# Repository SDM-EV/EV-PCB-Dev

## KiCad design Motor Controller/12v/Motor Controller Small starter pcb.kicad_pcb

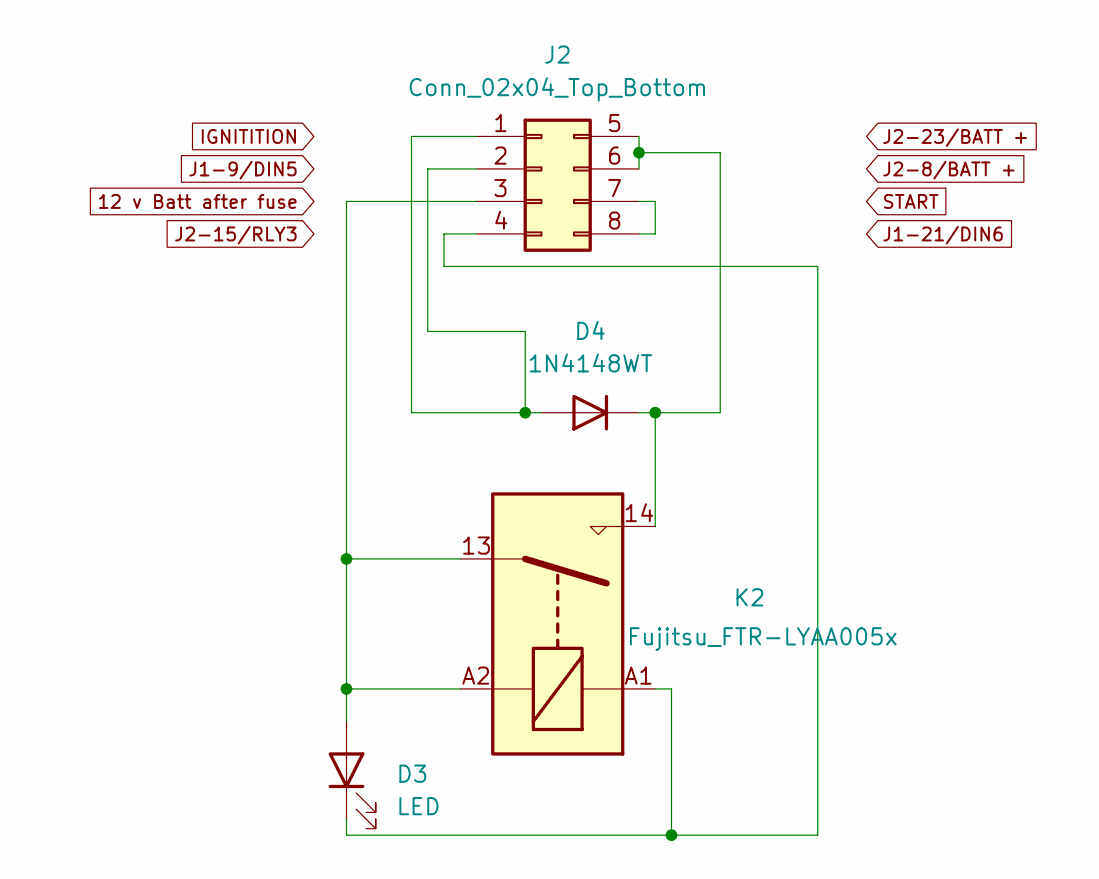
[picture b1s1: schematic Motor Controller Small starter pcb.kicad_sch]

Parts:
D3: LED; LED_D3.0mm
D4: 1N4148WT; D_SOD-523
J2: Conn_02x04_Top_Bottom; Molex_Mini-Fit_Jr_5566-08A2_2x04_P4.20mm_Vertical
K2: Fujitsu_FTR-LYAA005x; Relay_SPST-NO_Fujitsu_FTR-LYAA005x_FormA_Vertical

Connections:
unnamed: D3.2 (A), J2.3, K2.13, K2.A2
unnamed: D3.1 (K), J2.4, K2.A1
unnamed: D4.2 (A), J2.1, J2.2
unnamed: D4.1 (K), J2.5, J2.6, K2.14
unnamed: J2.7, J2.8

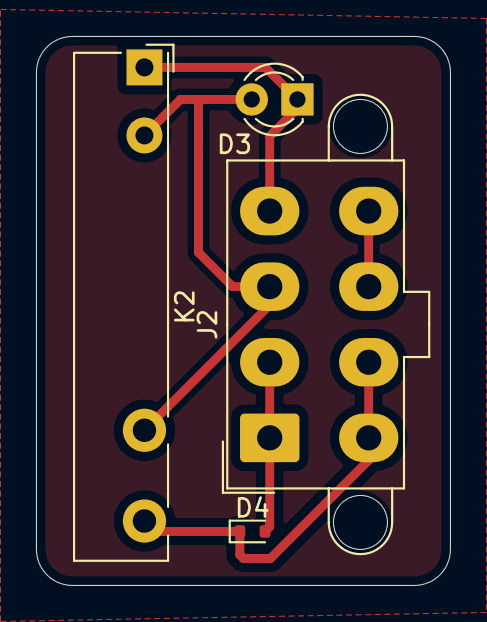
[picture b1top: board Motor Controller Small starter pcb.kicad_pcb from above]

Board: 2 copper layers, 23.0 x 30.5 mm, 4 parts (0 on the bottom side), 5 nets.

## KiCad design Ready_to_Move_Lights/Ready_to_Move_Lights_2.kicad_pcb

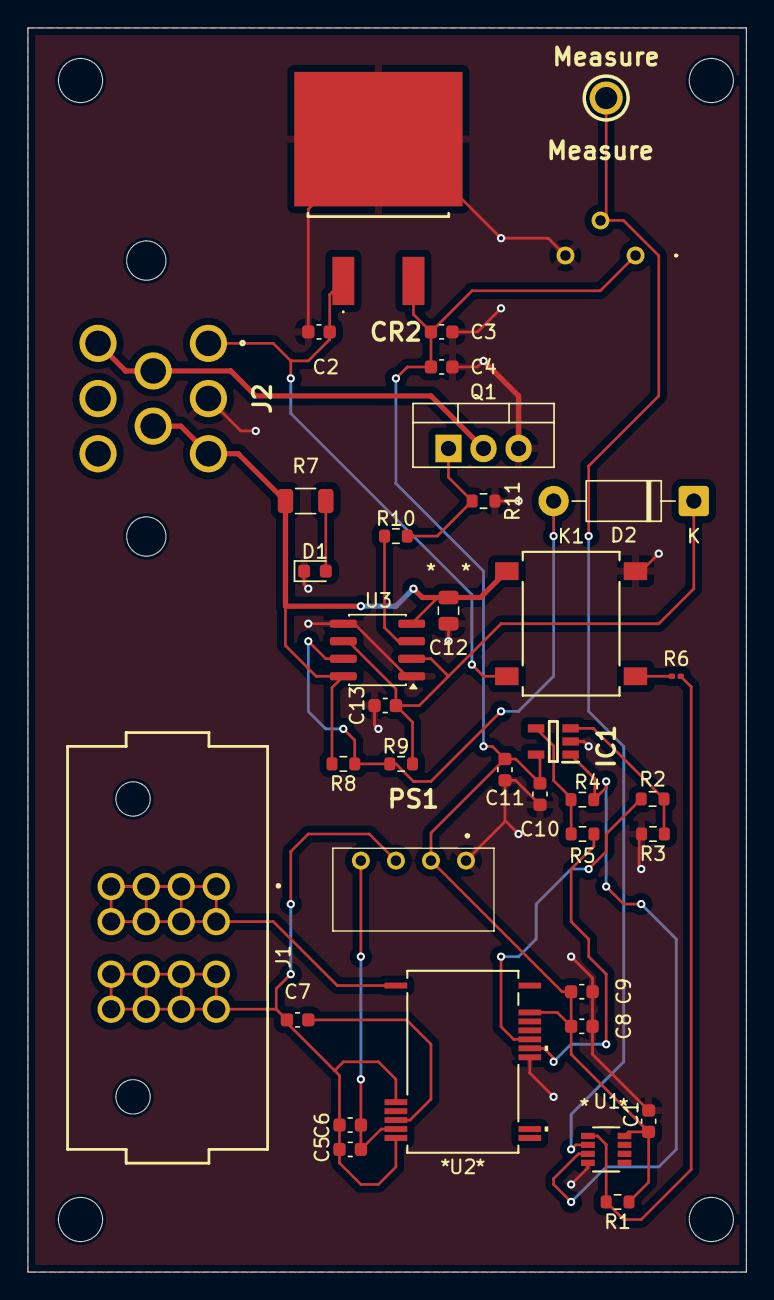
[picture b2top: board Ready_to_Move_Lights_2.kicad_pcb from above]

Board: 2 copper layers, 52.1 x 90.2 mm, 38 parts (0 on the bottom side), 22 nets.

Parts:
C1, C4, C5, C8, C10: 1uF; C_0603_1608Metric
C2: 0.33uF; C_0603_1608Metric
C3: 0.1uF; C_0603_1608Metric
C6, C9, C11: 100nF; C_0603_1608Metric
C7: 100pF; C_0603_1608Metric
C12: 0.01uF; C_0805_2012Metric
C13: 1.2uF; C_0603_1608Metric
CR2: L7805ACD2T-TR; L7805ACD2TTR
D1: RED LED; LED_0603_1608Metric
D2: 1N5817; D_DO-41_SOD81_P10.16mm_Horizontal
IC1: TLV2371QDBVRQ1; SOT95P280X145-5N
J1: PET-02-XX-X-VT-LC; SAMTEC_PET-02-XX-X-VT-LC
J2: 776280-1
K1: VORA1150-X017T; SOP_VORA1150-X017T_VIS
PS1: TEA_1-0505; TEA10505
Q1: IRLZ44N; TO-220-3_Vertical
R1: 200; R_0603_1608Metric
R2, R5, R11: 10k; R_0603_1608Metric
R3, R4: 50k; R_0603_1608Metric
R6: 1.2K; R_0201_0603Metric
R7: 499; R_1206_3216Metric
R8, R9: 200k; R_0603_1608Metric
R10: 470; R_0603_1608Metric
RED_TP1: 5005
U1: LM393LVQDDFRQ1; SOT-23-THIN8_DDF_TEX
U2: PAMC0381D10QDFXRQ1; SSOP15_DFX_TEX
U3: NE555D; SOIC-8_3.9x4.9mm_P1.27mm
VR1: 10k; 3386P1103TLF

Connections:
01: J1.01_1 (01), J1.01_2 (01), J1.01_3 (01), J1.01_4 (01), J1.01_5 (01), J1.01_6 (01), J1.01_7 (01), J1.01_8 (01), U2.1 (HVIN)
02: C5.1, C6.1, C7.1, J1.02_1 (02), J1.02_2 (02), J1.02_3 (02), J1.02_4 (02), J1.02_5 (02), J1.02_6 (02), J1.02_7 (02), J1.02_8 (02), PS1.3 (-VOUT), U2.2 (SNSN), U2.6 (GND1)
+5V: C1.1, C3.2, C4.2, C8.2, C9.2, C10.2, C11.2, CR2.3 (OUTPUT), IC1.5 (VDD), PS1.2 (+VIN_(VCC)), R1.1, U1.8 (V+), U2.14 (VDD2), VR1.1 (CCW)
+5VDD: C5.2, C6.2, PS1.4 (+VOUT), U2.5 (VDD1)
/12V Master: C2.2, CR2.1 (INPUT), J2.1, K1.4
/Light1+: C12.1, J2.3, J2.5, K1.3, R7.2, R8.2, U3.4 (R), U3.8 (VCC)
/Light1GND: J2.4, J2.6, Q1.2 (D)
/OUT_N: R5.2, U2.10 (OUTN)
/OUT_P: R2.1, U2.11 (OUTP)
/V_IND: R1.2, R6.2, U1.1 (OUT1)
/V_LOW_REF: RED_TP1.1, U1.2 (IN1-), VR1.2 (Wiper)
/V_OUT: IC1.1 (OUT), R4.2, U1.3 (IN1+)
GND: C1.2, C2.1, C3.1, C4.1, C8.1, C9.1, C10.1, C11.1, C12.2, C13.2, CR2.2 (GROUND), D1.1 (K), IC1.2 (GND), J2.2, K1.2, PS1.1 (-VIN_(GND)), Q1.3 (S), R3.2, R11.1, U1.4 (GND), U2.9 (GND2), U3.1 (GND), U3.5 (CV), VR1.3 (CW)
unnamed: D1.2 (A), R7.1
unnamed: D2.2 (A), R8.1, R9.1, U3.7 (DIS)
unnamed: C13.1, D2.1 (K), R9.2, U3.2 (TR), U3.6 (THR)
unnamed: IC1.3 (IN+), R2.2, R3.1
unnamed: IC1.4 (IN-), R4.1, R5.1
unnamed: K1.1, R6.1
unnamed: Q1.1 (G), R10.2, R11.2
unnamed: C7.2, U2.4 (SNSP)
unnamed: R10.1, U3.3 (Q)

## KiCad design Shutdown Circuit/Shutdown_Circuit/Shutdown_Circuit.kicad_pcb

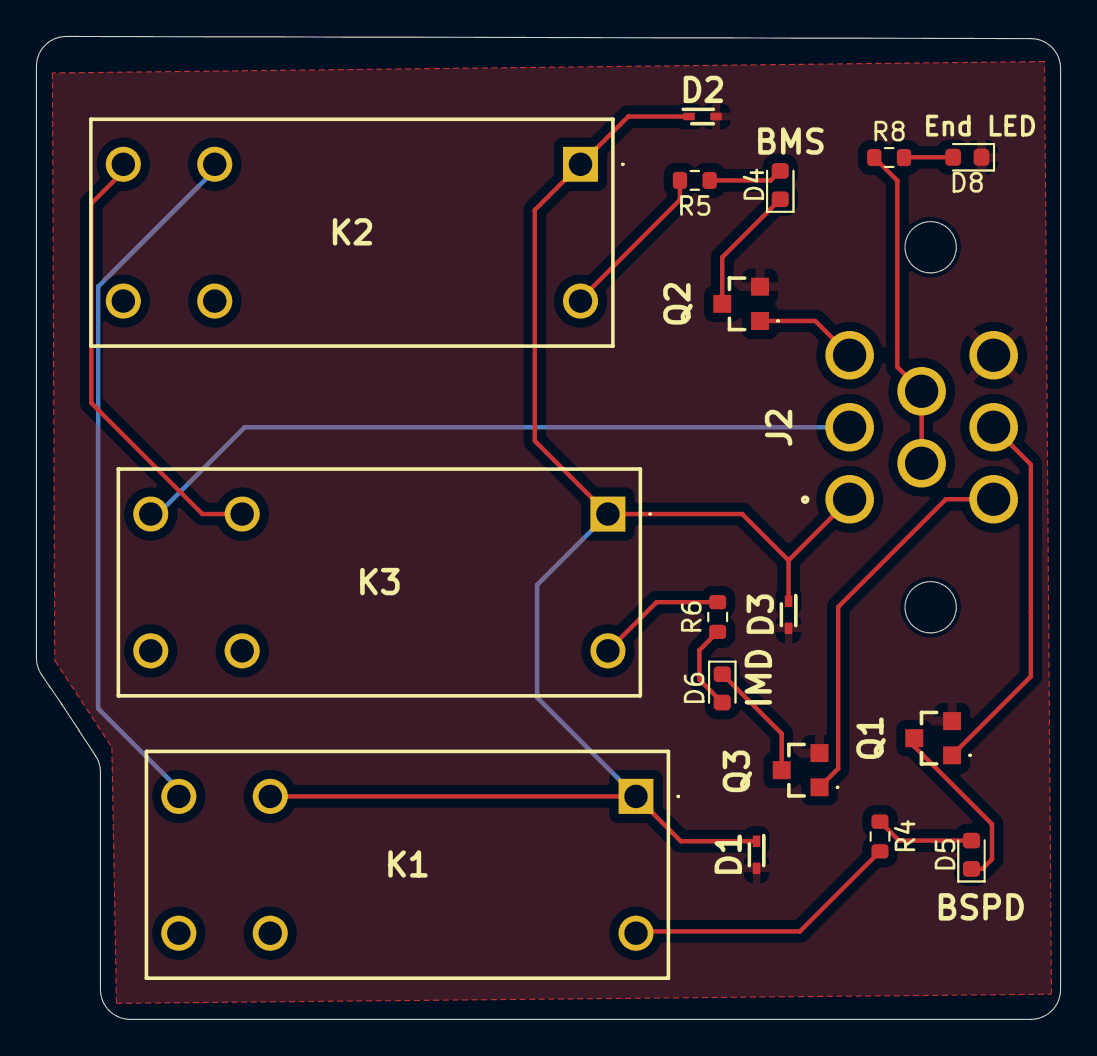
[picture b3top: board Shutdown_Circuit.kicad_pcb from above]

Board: 2 copper layers, 56.9 x 54.6 mm, 18 parts (0 on the bottom side), 19 nets.

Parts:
D1, D2, D3: D; SODFL1608X70N
D4: BMS; LED_0603_1608Metric
D5: BSPD; LED_0603_1608Metric
D6: IMD; LED_0603_1608Metric
D8: END_CHAIN; LED_0603_1608Metric
J2: 776280-1
K1, K2, K3: PR22-12V-400-1A; PR2212V4001A
Q1, Q2, Q3: ZXM61N02FTC
R4, R5, R6: 680; R_0603_1608Metric
R8: 220; R_0603_1608Metric

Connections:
+12V: D1.1 (K), D2.1 (K), D3.1 (K), J2.1, K1.1 (COIL_1), K1.2 (COM_1), K2.1 (COIL_1), K3.1 (COIL_1)
/BMS KILL SIGNAL: J2.3, Q2.1 (G)
/BSPD KILL SIGNAL: J2.7, Q1.1 (G)
/IMD KILL SIGNAL: J2.6, Q3.1 (G)
/RELAYS_OUT: J2.2, K3.3 (NO_1)
AIR SIGNAL: J2.4, J2.5, R8.1
GND: D1.2 (A), D2.2 (A), D3.2 (A), D8.1 (K), J2.8, Q1.3 (S), Q2.3 (S), Q3.3 (S)
unnamed: D4.2 (A), R5.1
unnamed: D4.1 (K), Q2.2 (D)
unnamed: D5.2 (A), R4.1
unnamed: D5.1 (K), Q1.2 (D)
unnamed: D6.2 (A), R6.1
unnamed: D6.1 (K), Q3.2 (D)
unnamed: D8.2 (A), R8.2
unnamed: K1.6 (COIL_2), R4.2
unnamed: K1.3 (NO_1), K2.2 (COM_1)
unnamed: K2.6 (COIL_2), R5.2
unnamed: K2.3 (NO_1), K3.2 (COM_1)
unnamed: K3.6 (COIL_2), R6.2

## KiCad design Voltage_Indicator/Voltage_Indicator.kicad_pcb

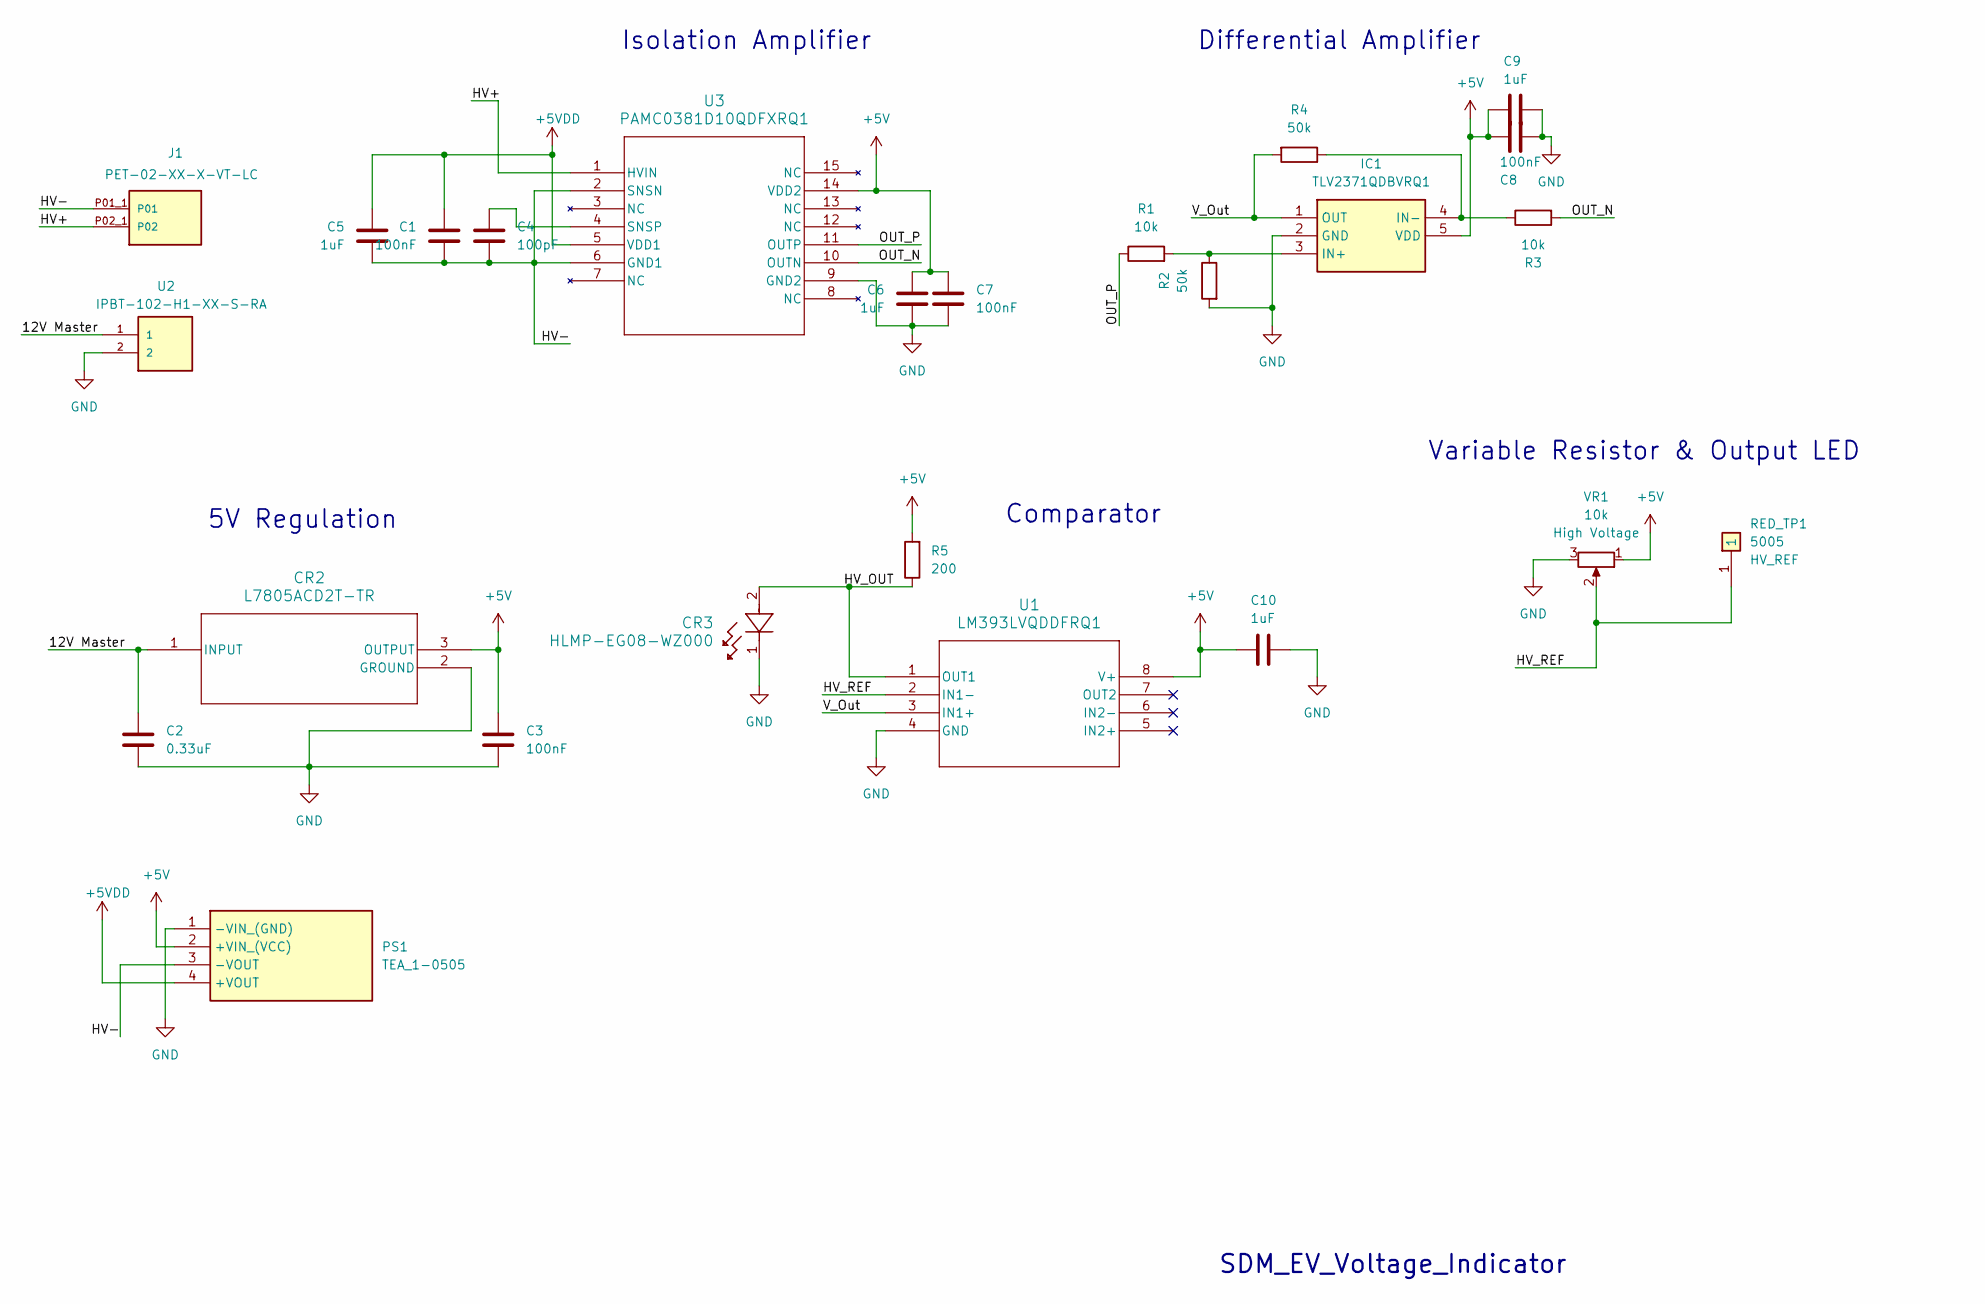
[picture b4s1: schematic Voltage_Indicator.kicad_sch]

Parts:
C1, C3, C7, C8: 100nF; C_0603_1608Metric
C2: 0.33uF; C_0603_1608Metric
C4: 100pF; C_0603_1608Metric
C5, C6, C9, C10: 1uF; C_0603_1608Metric
CR2: L7805ACD2T-TR; L7805ACD2TTR
CR3: HLMP-EG08-WZ000; LED_AVAGO_HLMP_XX08_AVA
IC1: TLV2371QDBVRQ1; SOT95P280X145-5N; Manufacturer_Part_Number TLV2371QDBVRQ1; Mouser Part Number 595-TLV2371QDBVRQ1
J1: PET-02-XX-X-VT-LC; SAMTEC_PES-02-01-X-RA-SD; PARTREV C
PS1: TEA_1-0505; TEA10505; Manufacturer_Part_Number TEA 1-0505; Mouser Part Number 495-TEA1-0505
R1, R3: 10k; R_0603_1608Metric
R2, R4: 50k; R_0603_1608Metric
R5: 200; R_0603_1608Metric
RED_TP1: 5005; Mouser Part Number 534-5005
U1: LM393LVQDDFRQ1; SOT-23-THIN8_DDF_TEX
U2: IPBT-102-H1-XX-S-RA
U3: PAMC0381D10QDFXRQ1; SSOP15_DFX_TEX
VR1: 10k; 3386P1103TLF; Mouser Part Number 652-3386P-1-103TLF

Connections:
+5V: C3.2, C6.2, C7.2, C8.2, C9.2, C10.2, CR2.3 (OUTPUT), IC1.5 (VDD), PS1.2 (+VIN_(VCC)), R5.2, U1.8 (V+), U3.14 (VDD2), VR1.1 (CCW)
+5VDD: C1.2, C5.2, PS1.4 (+VOUT), U3.5 (VDD1)
/12V Master: C2.2, CR2.1 (INPUT), U2.1
/HV+: J1.P02_1 (P02), U3.1 (HVIN)
/HV-: C1.1, C4.1, C5.1, J1.P01_1 (P01), PS1.3 (-VOUT), U3.2 (SNSN), U3.6 (GND1)
/HV_OUT: CR3.2, R5.1, U1.1 (OUT1)
/HV_REF: RED_TP1.1, U1.2 (IN1-), VR1.2 (Wiper)
/OUT_N: R3.2, U3.10 (OUTN)
/OUT_P: R1.1, U3.11 (OUTP)
/V_Out: IC1.1 (OUT), R4.2, U1.3 (IN1+)
GND: C2.1, C3.1, C6.1, C7.1, C8.1, C9.1, C10.1, CR2.2 (GROUND), CR3.1, IC1.2 (GND), PS1.1 (-VIN_(GND)), R2.2, U1.4 (GND), U2.2, U3.9 (GND2), VR1.3 (CW)
unnamed: IC1.3 (IN+), R1.2, R2.1
unnamed: IC1.4 (IN-), R3.1, R4.1
unnamed: C4.2, U3.4 (SNSP)

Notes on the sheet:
Isolation Amplifier
Variable Resistor & Output LED
Differential Amplifier
Comparator
SDM_EV_Voltage_Indicator
5V Regulation

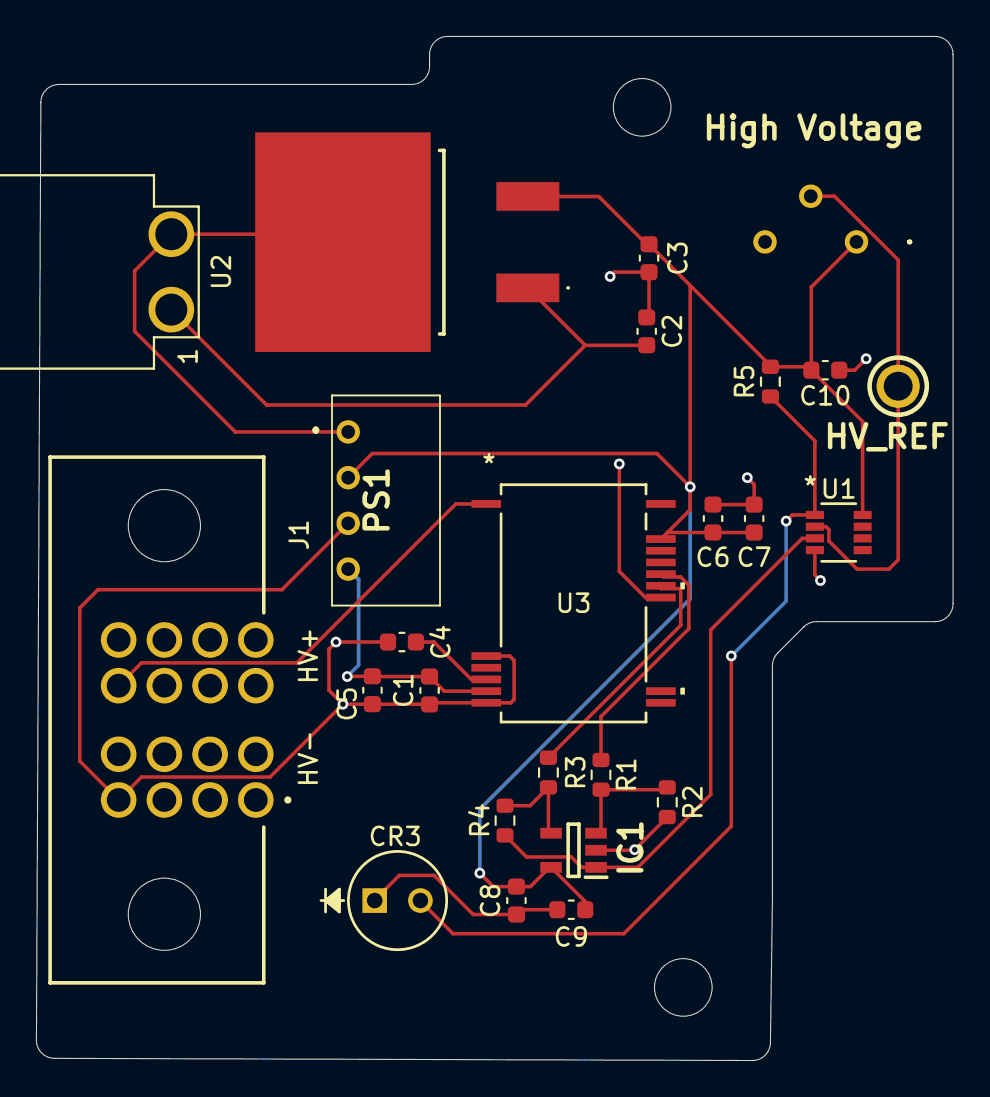
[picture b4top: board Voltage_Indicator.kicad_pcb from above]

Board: 2 copper layers, 50.9 x 56.9 mm, 25 parts (0 on the bottom side), 14 nets.

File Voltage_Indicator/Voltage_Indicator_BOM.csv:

"Reference","Qty","Value","DNP","Exclude from BOM","Exclude from Board","Footprint","Datasheet"
"C1,C3,C7,C8","4","100nF","","","","Capacitor_SMD:C_0603_1608Metric","~"
"C2","1","0.33uF","","","","Capacitor_SMD:C_0603_1608Metric","~"
"C4","1","100pF","","","","Capacitor_SMD:C_0603_1608Metric","~"
"C5,C6,C9,C10","4","1uF","","","","Capacitor_SMD:C_0603_1608Metric","~"
"CR2","1","L7805ACD2T-TR","","","","Footprints:L7805ACD2TTR","https://www.st.com/resource/en/datasheet/l78.pdf"
"CR3","1","HLMP-EG08-WZ000","","","","Footprints:LED_AVAGO_HLMP_XX08_AVA","HLMP-EG08-WZ000"
"IC1","1","TLV2371QDBVRQ1","","","","Footprints:SOT95P280X145-5N","http://www.ti.com/lit/gpn/tlv2371-q1"
"J1","1","PET-02-XX-X-VT-LC","","","","Footprints:SAMTEC_PES-02-01-X-RA-SD",""
"R1,R3","2","10k","","","","Resistor_SMD:R_0603_1608Metric","~"
"R2,R4","2","50k","","","","Resistor_SMD:R_0603_1608Metric","~"
"R5","1","200","","","","Resistor_SMD:R_0603_1608Metric","~"
"RED_TP1","1","5005","","","","SDM_MiscFootprint:5005","http://www.keyelco.com/product-pdf.cfm?p=1314"
"U1","1","LM393LVQDDFRQ1","","","","Footprints:SOT-23-THIN8_DDF_TEX","https://www.ti.com/lit/gpn/lm393lv-q1"
"U2","1","IPBT-102-H1-XX-S-RA","","","","Footprints:IPBT-102-H1-XX-S-RA",""
"U3","1","PAMC0381D10QDFXRQ1","","","","Footprints:SSOP15_DFX_TEX","https://www.ti.com/lit/gpn/amc0381d-q1"
"VR1","1","10k","","","","SDM_MiscFootprint:3386P1103TLF","https://www.mouser.com/datasheet/2/54/3386-776606.pdf"

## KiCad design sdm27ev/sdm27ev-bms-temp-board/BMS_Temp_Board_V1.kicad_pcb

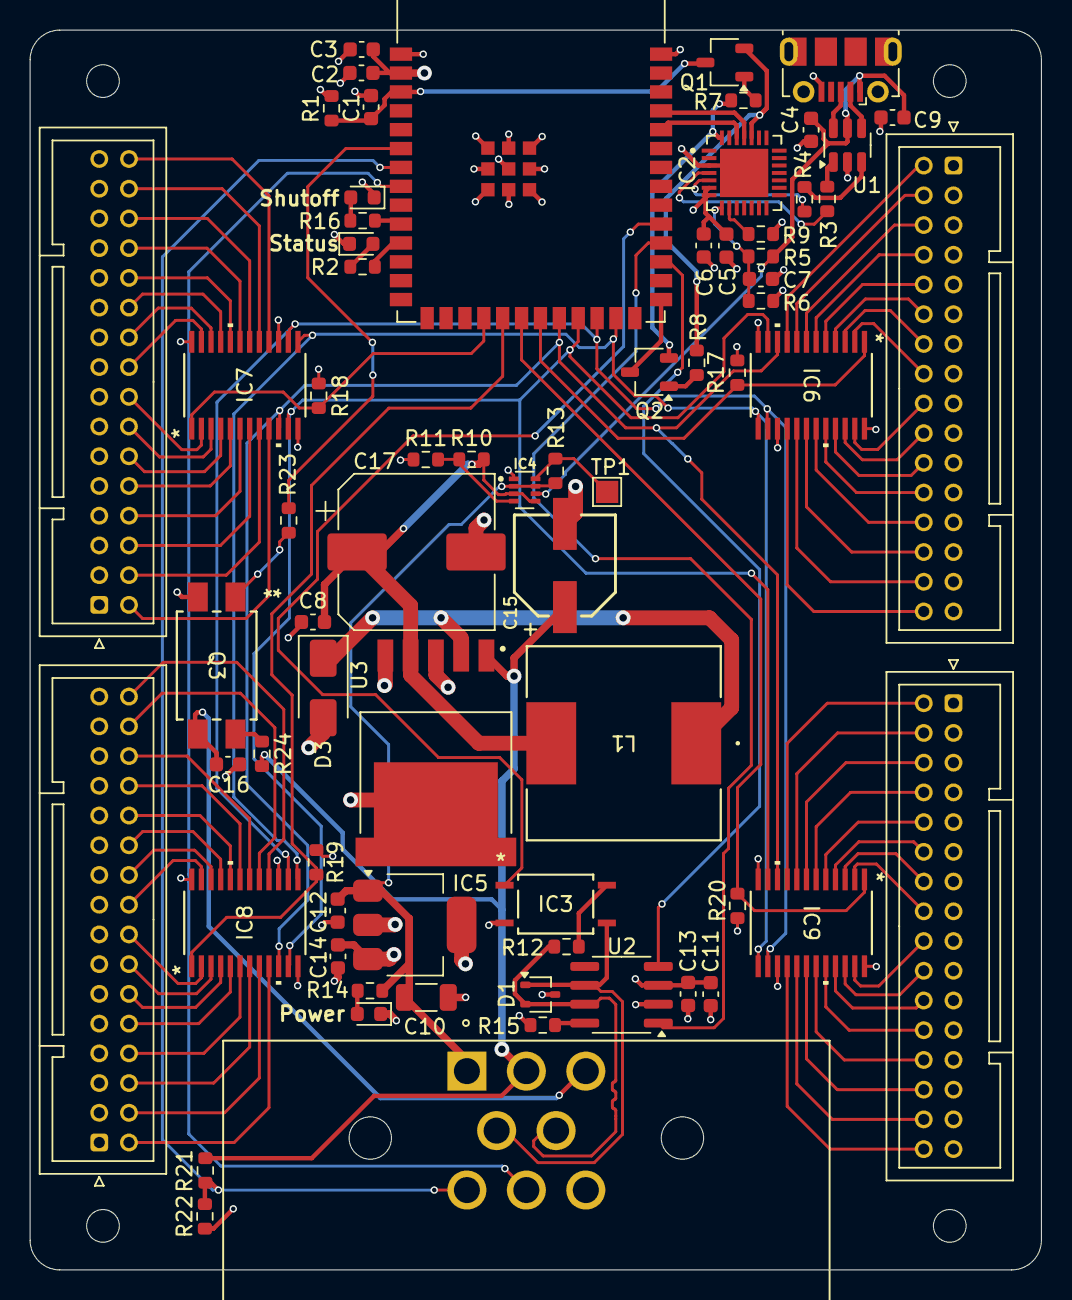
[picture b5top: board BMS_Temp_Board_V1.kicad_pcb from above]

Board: 4 copper layers, 68.0 x 83.4 mm, 73 parts (0 on the bottom side), 115 nets.

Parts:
C1, C4, C7, C8, C9: 1uF; C_0603_1608Metric
C2, C12, C14: 10uF; C_0603_1608Metric
C3, C6, C11, C13: 100nF; C_0603_1608Metric
C5: 4.7uF; C_0603_1608Metric
C10: 100uF; C_1206_3216Metric
C15: 100uF; WCAP-ASLI_6.3X7.7_DXL_
C16: 0.1uF; C_0603_1608Metric
C17: 330uF; CP_Elec_10x10
D1: ESDCAN03-2BWY; SOT-323_SC-70
D3: SS14; D_SMA
H1, H2, H3, H4: MountingHole; MountingHole_2.2mm_M2
IC1: ESP32-S3-WROOM-1-N8R8; XCVR_ESP32S3WROOM1N8R8
IC2: CP2102N-A02-GQFN28; QFN50P500X500X80-29N
IC3: TLP175A_TPL,E; 4pin SO6TLP17XX_TOS
IC4: TPS2116DRLR; SOTFL50P160X60-8N
IC5: MIC37100-3.3WS; SOT-223
IC6, IC7, IC8, IC9: CD74HC4067PWR; TSSOP24_4P5X7P9_TEX
J1: ESP_USB; USB_Micro-B_Molex-105017-0001
J2, J3, J4, J5: B32B-PUDSS-1_LF__SN_; JST_PUD_B32B-PUDSS_2x16_P2.00mm_Vertical_PN
J6: 776279-1; TE_776279-1
L1: 330uH; IND_SPD127R_API
LED1: GREEN; LED_0603_1608Metric
LED2: 150060RS75000; LED_0603_1608Metric
LED3: RED; LED_0603_1608Metric
Q1, Q2: MMBT2222LT1G; TSOT-23
Q3: LTV-817S-TA1; LTV-817S_LTO
R1, R7, R8, R10, R11, R13, R15, R17, R18, R19, R20, R21, R24: 10k; R_0603_1608Metric
R2, R16, R23: 220; R_0603_1608Metric
R3, R4: 27; R_0603_1608Metric
R5: 22.1K; R_0603_1608Metric
R6: 47.5K; R_0603_1608Metric
R9: 1k; R_0603_1608Metric
R12: 120; R_0603_1608Metric
R14: 68; R_0603_1608Metric
R22: 3.3k; R_0603_1608Metric
TP1: ST_5V; TestPoint_Pad_1.5x1.5mm
U1: USBLC6-2SC6; SOT-23-6
U2: SN65HVD230; SOIC-8_3.9x4.9mm_P1.27mm
U3: LM2575HVS-5.0_NOPB; VREG_LM2575HVS-5.0_NOPB

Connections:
+3.3V: C2.2, C3.2, C5.1, C6.2, C11.1, C13.1, C14.2, IC1.2 (3V3), IC2.6 (VDD), IC2.7 (VREGIN), IC5.3 (OUT), IC6.24 (VCC), IC7.24 (VCC), IC8.24 (VCC), IC9.24 (VCC), J2.1, J2.3, J2.5, J2.7, J2.9, J2.11, J2.13, J2.15, J2.17, J2.19, J2.21, J2.23, J2.25, J2.27, J2.29, J2.31, J3.1, J3.3, J3.5, J3.7, J3.9, J3.11, J3.13, J3.15, J3.17, J3.19, J3.21, J3.23, J3.25, J3.27, J3.29, J3.31, J4.1, J4.3, J4.5, J4.7, J4.9, J4.11, J4.13, J4.15, J4.17, J4.19, J4.21, J4.23, J4.25, J4.27, J4.29, J4.31, J5.1, J5.3, J5.5, J5.7, J5.9, J5.11, J5.13, J5.15, J5.17, J5.19, J5.21, J5.23, J5.25, J5.27, J5.29, J5.31, R1.1, R9.2, U2.3 (VCC)
+5V: C10.1, C12.2, IC4.2 (VOUT), IC4.7 (VOUT), IC5.1 (IN), J6.1, R13.1, R14.1
+12V: C15.1, J6.2, R21.1, R24.2, U3.1 (VIN)
/CAN+: D1.2, J6.5, R12.2, U2.7 (CANH)
/CAN-: D1.1, IC3.4, J6.4, U2.6 (CANL)
/CAN_CTX: IC1.29 (IO36), U2.4 (R)
/CAN_RTX: IC1.30 (IO37), U2.1 (D)
/CAN_TERM: IC1.31 (IO38), IC3.1
/CHIP_PU: C1.1, IC1.3 (EN), Q1.3 (C), R1.2
/GPIO0: IC1.27 (IO0), Q2.3 (C)
/IO15: IC1.8 (IO15), J6.7
/MUX1: IC1.21 (IO13), IC6.1 (COM), R17.1
/MUX2: IC1.18 (IO10), IC7.1 (COM), R18.1
/MUX3: IC1.19 (IO11), IC8.1 (COM), R19.1
/MUX4: IC1.20 (IO12), IC9.1 (COM), R20.1
/MUX_S0: IC1.22 (IO14), IC6.10 (S0), IC7.10 (S0), IC8.10 (S0), IC9.10 (S0)
/MUX_S1: IC1.23 (IO21), IC6.11 (S1), IC7.11 (S1), IC8.11 (S1), IC9.11 (S1)
/MUX_S2: IC1.24 (IO47), IC6.14 (S2), IC7.14 (S2), IC8.14 (S2), IC9.14 (S2)
/MUX_S3: IC1.25 (IO48), IC6.13 (S3), IC7.13 (S3), IC8.13 (S3), IC9.13 (S3)
/ORION: IC1.7 (IO7), J6.6, R21.2, R22.1
/PROG_D+: IC2.4 (D+), R3.2
/PROG_D-: IC2.5 (D-), R4.1
/PWR_LED: LED2.2 (A), R14.2
/RSTB: IC2.9 (RSTB), R9.1
/SHUTDOWN_IND: IC1.10 (IO17), R16.1
/SHUTOFF: IC1.6 (IO6), R23.1
/SHUTOFF_ISO: C16.1, J6.3, Q3.3
/ST: IC4.8 (ST), R13.2, TP1.1
/U0RXD: IC1.36 (RXD0), IC2.26 (TXD)
/U0TXD: IC1.37 (TXD0), IC2.25 (RXD)
/USBM_D+: J1.3 (D+), U1.6 (I/O1)
/USBM_D-: J1.2 (D-), U1.4 (I/O2)
/USER_LED: IC1.11 (IO18), R2.1
/USR_LED_RSTR: LED1.2 (A), R2.2
GND: C1.2, C2.1, C3.1, C4.1, C5.2, C6.1, C7.2, C8.1, C9.1, C10.2, C11.2, C12.1, C13.2, C14.1, C15.2, C16.2, C17.2, D1.3, D3.2 (A), IC1.1 (GND_1), IC1.40 (GND_2), IC1.41 (GND_3), IC1.42 (GND_4), IC1.43 (GND_5), IC1.44 (GND_6), IC1.45 (GND_7), IC1.46 (GND_8), IC1.47 (GND_9), IC1.48 (GND_10), IC1.49 (GND_11), IC2.3 (GND), IC2.29 (BGND), IC3.3, IC4.1 (GND), IC5.2 (GND_1), IC5.4 (GND_2), IC6.12 (GND), IC6.15 (~E), IC7.12 (GND), IC7.15 (~E), IC8.12 (GND), IC8.15 (~E), IC9.12 (GND), IC9.15 (~E), J1.5 (GND), J6.8, LED1.1 (K), LED2.1 (K), LED3.1 (K), Q3.2, R6.2, R11.1, R15.1, R17.2, R18.2, R19.2, R20.2, R22.2, U1.2 (GND), U2.2 (GND), U3.3 (GROUND), U3.5 (~ON/OFF), U3.6 (GROUND__1)
unnamed: D3.1 (K), L1.1, U3.2 (OUTPUT)
unnamed: IC2.28 (DTR), Q2.2 (E), R7.2
unnamed: IC2.24 (RTS), Q1.2 (E), R8.2
unnamed: C7.1, IC2.8 (VBUS), R5.1, R6.1
unnamed: IC3.6, R12.1
unnamed: IC4.4 (PR1), R10.1, R11.2
unnamed: IC6.9 (I0), J2.2
unnamed: IC6.8 (I1), J2.4
unnamed: IC6.7 (I2), J2.6
unnamed: IC6.6 (I3), J2.8
unnamed: IC6.5 (I4), J2.10
unnamed: IC6.4 (I5), J2.12
unnamed: IC6.3 (I6), J2.14
unnamed: IC6.2 (I7), J2.16
unnamed: IC6.23 (I8), J2.18
unnamed: IC6.22 (I9), J2.20
unnamed: IC6.21 (I10), J2.22
unnamed: IC6.20 (I11), J2.24
unnamed: IC6.19 (I12), J2.26
unnamed: IC6.18 (I13), J2.28
unnamed: IC6.17 (I14), J2.30
unnamed: IC6.16 (I15), J2.32
unnamed: IC7.9 (I0), J3.2
unnamed: IC7.8 (I1), J3.4
unnamed: IC7.7 (I2), J3.6
unnamed: IC7.6 (I3), J3.8
unnamed: IC7.5 (I4), J3.10
unnamed: IC7.4 (I5), J3.12
unnamed: IC7.3 (I6), J3.14
unnamed: IC7.2 (I7), J3.16
unnamed: IC7.23 (I8), J3.18
unnamed: IC7.22 (I9), J3.20
unnamed: IC7.21 (I10), J3.22
unnamed: IC7.20 (I11), J3.24
unnamed: IC7.19 (I12), J3.26
unnamed: IC7.18 (I13), J3.28
unnamed: IC7.17 (I14), J3.30
unnamed: IC7.16 (I15), J3.32
unnamed: IC8.9 (I0), J4.2
unnamed: IC8.8 (I1), J4.4
unnamed: IC8.7 (I2), J4.6
unnamed: IC8.6 (I3), J4.8
unnamed: IC8.5 (I4), J4.10
unnamed: IC8.4 (I5), J4.12
unnamed: IC8.3 (I6), J4.14
unnamed: IC8.2 (I7), J4.16
unnamed: IC8.23 (I8), J4.18
unnamed: IC8.22 (I9), J4.20
unnamed: IC8.21 (I10), J4.22
unnamed: IC8.20 (I11), J4.24
unnamed: IC8.19 (I12), J4.26
unnamed: IC8.18 (I13), J4.28
unnamed: IC8.17 (I14), J4.30
unnamed: IC8.16 (I15), J4.32
unnamed: IC9.9 (I0), J5.2
unnamed: IC9.8 (I1), J5.4
unnamed: IC9.7 (I2), J5.6
unnamed: IC9.6 (I3), J5.8
unnamed: IC9.5 (I4), J5.10
unnamed: IC9.4 (I5), J5.12
unnamed: IC9.3 (I6), J5.14
unnamed: IC9.2 (I7), J5.16
unnamed: IC9.23 (I8), J5.18
unnamed: IC9.22 (I9), J5.20
unnamed: IC9.21 (I10), J5.22
unnamed: IC9.20 (I11), J5.24
unnamed: IC9.19 (I12), J5.26
unnamed: IC9.18 (I13), J5.28
unnamed: IC9.17 (I14), J5.30
unnamed: IC9.16 (I15), J5.32
unnamed: LED3.2 (A), R16.2
unnamed: Q1.1 (B), R7.1
unnamed: Q2.1 (B), R8.1
unnamed: Q3.1, R23.2
unnamed: Q3.4, R24.1
unnamed: R3.1, U1.1 (I/O1)
unnamed: R4.2, U1.3 (I/O2)
unnamed: R15.2, U2.8 (Rs)
VBUS: C4.2, C9.2, IC4.6 (VIN2), J1.1 (VBUS), R5.2, U1.5 (VBUS)
VCC: C8.2, C17.1, IC4.3 (VIN1), IC4.5 (MODE), L1.2, R10.2, U3.4 (FEEDBACK)

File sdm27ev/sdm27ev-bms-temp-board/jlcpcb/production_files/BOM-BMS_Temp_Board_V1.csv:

Comment,Designator,Footprint,LCSC,Quantity
1uF,C9,C_0603_1608Metric,,1
USBLC6-2SC6,U1,SOT-23-6,,1
10k,R21,R_0603_1608Metric,,1
1uF,C8,C_0603_1608Metric,,1
100uF,C15,WCAP-ASLI_6.3X7.7_DXL_,,1
MMBT2222LT1G,Q2,TSOT-23,,1
10uF,C12,C_0603_1608Metric,,1
150060RS75000,LED2,LED_0603_1608Metric,,1
1uF,C7,C_0603_1608Metric,,1
SN65HVD230,U2,SOIC-8_3.9x4.9mm_P1.27mm,,1
CD74HC4067PWR,IC7,TSSOP24_4P5X7P9_TEX,,1
68,R14,R_0603_1608Metric,,1
RED,LED3,LED_0603_1608Metric,,1
10k,R11,R_0603_1608Metric,,1
10k,R24,R_0603_1608Metric,,1
10k,R19,R_0603_1608Metric,,1
330uF,C17,CP_Elec_10x10,,1
MMBT2222LT1G,Q1,TSOT-23,,1
220,R16,R_0603_1608Metric,,1
CD74HC4067PWR,IC8,TSSOP24_4P5X7P9_TEX,,1
10k,R18,R_0603_1608Metric,,1
ESDCAN03-2BWY,D1,SOT-323_SC-70,,1
220,R23,R_0603_1608Metric,,1
LM2575HVS-5.0_NOPB,U3,VREG_LM2575HVS-5.0_NOPB,,1
27,R4,R_0603_1608Metric,,1
B32B-PUDSS-1_LF__SN_,J3,JST_PUD_B32B-PUDSS_2x16_P2.00mm_Vertical_PN,,1
330uH,L1,IND_SPD127R_API,,1
CD74HC4067PWR,IC9,TSSOP24_4P5X7P9_TEX,,1
10k,R1,R_0603_1608Metric,,1
SS14,D3,D_SMA,,1
22.1K,R5,R_0603_1608Metric,,1
LTV-817S-TA1,Q3,LTV-817S_LTO,,1
B32B-PUDSS-1_LF__SN_,J4,JST_PUD_B32B-PUDSS_2x16_P2.00mm_Vertical_PN,,1
10uF,C14,C_0603_1608Metric,,1
100nF,C11,C_0603_1608Metric,,1
B32B-PUDSS-1_LF__SN_,J5,JST_PUD_B32B-PUDSS_2x16_P2.00mm_Vertical_PN,,1
100nF,C6,C_0603_1608Metric,,1
10k,R10,R_0603_1608Metric,,1
B32B-PUDSS-1_LF__SN_,J2,JST_PUD_B32B-PUDSS_2x16_P2.00mm_Vertical_PN,,1
MIC37100-3.3WS,IC5,SOT-223,,1
1uF,C4,C_0603_1608Metric,,1
1uF,C1,C_0603_1608Metric,,1
10k,R7,R_0603_1608Metric,,1
100uF,C10,C_1206_3216Metric,,1
0.1uF,C16,C_0603_1608Metric,,1
27,R3,R_0603_1608Metric,,1
10k,R13,R_0603_1608Metric,,1
"TLP175A_TPL,E",IC3,4pin SO6TLP17XX_TOS,,1
ESP32-S3-WROOM-1-N8R8,IC1,XCVR_ESP32S3WROOM1N8R8,,1
10k,R17,R_0603_1608Metric,,1
CP2102N-A02-GQFN28,IC2,QFN50P500X500X80-29N,,1
TPS2116DRLR,IC4,SOTFL50P160X60-8N,,1
47.5K,R6,R_0603_1608Metric,,1
ESP_USB,J1,USB_Micro-B_Molex-105017-0001,,1
120,R12,R_0603_1608Metric,,1
10k,R15,R_0603_1608Metric,,1
100nF,C13,C_0603_1608Metric,,1
CD74HC4067PWR,IC6,TSSOP24_4P5X7P9_TEX,,1
10k,R8,R_0603_1608Metric,,1
3.3k,R22,R_0603_1608Metric,,1
776279-1,J6,TE_776279-1,,1
ST_5V,TP1,TestPoint_Pad_1.5x1.5mm,,1
10uF,C2,C_0603_1608Metric,,1
GREEN,LED1,LED_0603_1608Metric,,1
100nF,C3,C_0603_1608Metric,,1
10k,R20,R_0603_1608Metric,,1
220,R2,R_0603_1608Metric,,1
1k,R9,R_0603_1608Metric,,1
4.7uF,C5,C_0603_1608Metric,,1

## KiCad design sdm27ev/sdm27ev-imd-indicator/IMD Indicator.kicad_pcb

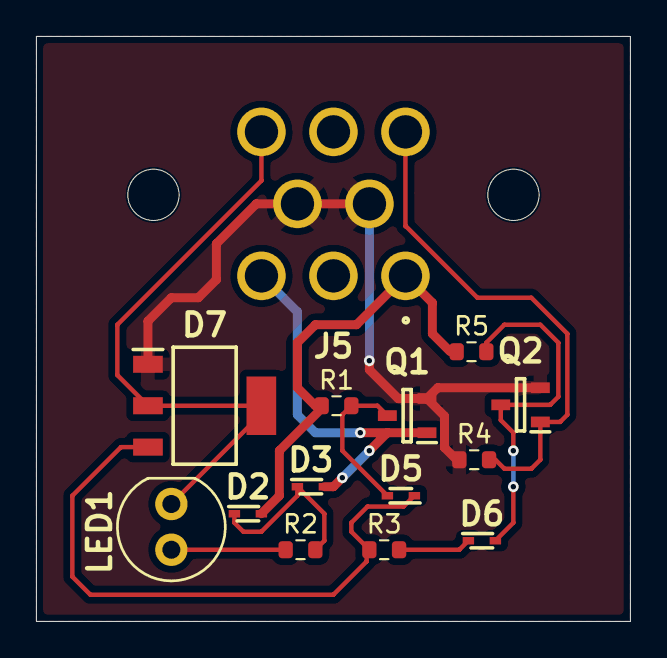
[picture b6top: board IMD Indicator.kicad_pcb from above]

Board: 2 copper layers, 33.0 x 32.5 mm, 14 parts (0 on the bottom side), 11 nets.

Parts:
D2, D3, D5, D6: BAT54XV2T1G; SODFL1608X70N
D7: X0202MN_5BA4; SOT230P700X190-4N
J5: 776280-1
LED1: HLMP-EG30-NR000; LED_5MM
Q1, Q2: 2N7002,215; SOT95P230X110-3N
R1, R5: 10k; R_0603_1608Metric
R2: 510; R_0603_1608Metric
R3: 1k; R_0603_1608Metric
R4: 2.2k; R_0603_1608Metric

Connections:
/12V IGNITION: D2.2 (A), J5.1, R1.1, R5.1
/12V MASTER: D3.2 (A), J5.3, Q1.1 (G)
/IMD_LOGIC_SIGNAL: J5.6, Q2.1 (G), R4.2
/SCR Gate: D5.1 (K), D7.3 (G), R3.1
GND: D7.1 (K), J5.4, J5.5, Q1.2 (S), Q2.2 (S), R4.1
IMD KILL SIGNAL: D7.2 (A_1), D7.4 (A_2), J5.8, LED1.1 (K)
unnamed: D2.1 (K), D3.1 (K), R2.1
unnamed: D5.2 (A), Q1.3 (D), R1.2
unnamed: D6.2 (A), Q2.3 (D), R5.2
unnamed: D6.1 (K), R3.2
unnamed: LED1.2 (A), R2.2

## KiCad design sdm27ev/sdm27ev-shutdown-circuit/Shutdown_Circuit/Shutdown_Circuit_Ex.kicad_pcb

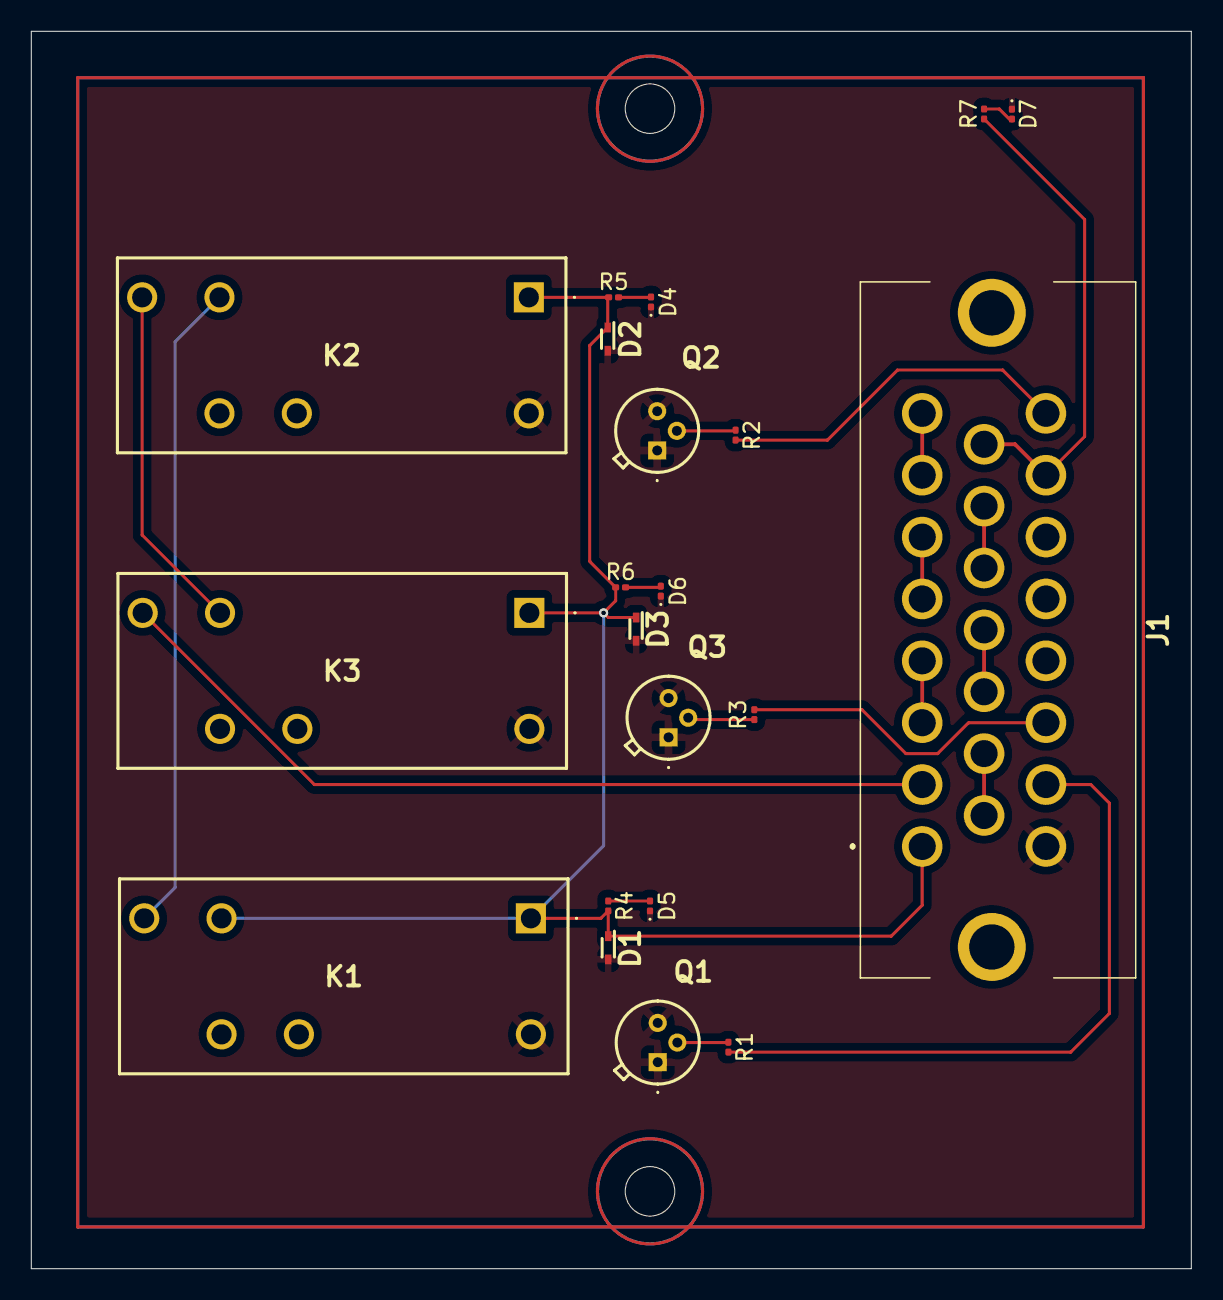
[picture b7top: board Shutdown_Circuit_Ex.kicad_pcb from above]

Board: 2 copper layers, 75.0 x 80.0 mm, 21 parts (0 on the bottom side), 22 nets.

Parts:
D1, D2, D3: D; SODFL1608X70N
D4: BMS; LED_0201_0603Metric
D5: BSPD; LED_0201_0603Metric
D6: IMD; LED_0201_0603Metric
D7: END_CHAIN; LED_0201_0603Metric
J1: 776087-1; 7760871
K1, K2, K3: V23047A1012A511
Q1, Q2, Q3: 2N2222
R1, R2, R3: 680; R_0201_0603Metric
R4, R5, R6, R7: 220; R_0201_0603Metric

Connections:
+12V: D1.1 (K), D2.1 (K), D3.1 (K), J1.1, K1.1 (COIL_1), K1.14 (COM_1), K2.1 (COIL_1), K3.1 (COIL_1), R4.2, R5.2, R6.2
/RELAYS_OUT: J1.2, K3.13 (NO_1)
BMS KILL SIGNAL: J1.23, R2.2
BSPD KILL SIGNAL: J1.17, R1.2
GND: D1.2 (A), D2.2 (A), D3.2 (A), D4.1 (K), D5.1 (K), D6.1 (K), D7.1 (K), J1.16, K1.2 (COIL_2), K2.2 (COIL_2), K3.2 (COIL_2), Q1.1 (E), Q1.3 (C), Q2.1 (E), Q2.3 (C), Q3.1 (E), Q3.3 (C)
IMD KILL SIGNAL: J1.18, R3.2
unnamed: D4.2 (A), R5.1
unnamed: D5.2 (A), R4.1
unnamed: D6.2 (A), R6.1
unnamed: D7.2 (A), R7.1
unnamed: J1.3, J1.4
unnamed: J1.5, J1.6
unnamed: J1.7, J1.8
unnamed: J1.9, J1.10
unnamed: J1.11, J1.12
unnamed: J1.13, J1.14
unnamed: K1.13 (NO_1), K2.14 (COM_1)
unnamed: K2.13 (NO_1), K3.14 (COM_1)
unnamed: Q1.2 (B), R1.1
unnamed: Q2.2 (B), R2.1
unnamed: Q3.2 (B), R3.1
SHUTDOWN_OUT: J1.15, J1.22, R7.2
